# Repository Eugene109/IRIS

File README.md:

> A low-cost quadcopter platform designed for autonomous swarm operations.

## Overview
IRIS is centered around a mass-manufacturable low-cost PCB, containing a flight controller and 4 ESCs. Designed with the idea of delivering Skittles autonomously, IRIS is built from the ground-up for autonomous operation in swarms. With a rich sensor set and high degree of customizability, IRIS represents an accessible, low-cost entry into the world of autonomous and swarm drone operations. I began this project because I found a lack of accessible drone designs that are for more than just 'fun FPV flying', and I wanted to be able to program a drone to do cool things. IRIS represents a rethinking of small drone design, believing that small drones can and should be autonomous and that everyone should be able to program a drone.

## Features
 - STM32H743 MCU
 - IMU, Barometer, Magnetometer, GPS
 - Integrated 4-in-1 ESC with sensorless drive
 - OV2640 camera for computer vision
 - 2.4GHz Radio Transciever + nanoELRS header
 - 2S LiPo input, XT60 connector
 - 3D-printed frame

## Table of Contents
- [Design Features](#design-features)
  - [Flight Controller Design](#flight-controller-design)
  - [ESC Design](#esc-design)
  - [Frame Design](#frame-design)
- [Getting Started](#getting-started)
- [PCB Assembly](#pcb-assembly)
- [Bill of Materials](#bill-of-materials)
- [Drone Assembly](#drone-assembly)
- [Firmware](#firmware)
- [Roadmap](#roadmap)

## Hack Club Magazine Page

## Design Features

### Flight Controller Design
<p align="center">
  
&nbsp; &nbsp; &nbsp; &nbsp;
  
</p>

[Schematic](./pcb/schematics/Flight_Controller_Schematic.svg)

The PCB design features a 4-layer PCB stackup for lowered manufacturing costs, with a (nearly) continuous ground plane for reduced RF interference. The area under the MCU and core sensors also feature a continuous 3.3V power plane. The high voltage and current for the ESCs are routed on large copper pours on the bottom layer, with cross-layer connections connected by suture vias.

The total board dimensions are 3.650" by 2.856", a little larger than a credit card.

The main flight controller MCU is programmable over USB. The 4 ESC MCUs require a serial programmer, with ground, rx and tx exposed on header pins. All MCUs have a dedicated switch for a physical boot selector.

### ESC Design

[Schematic](./pcb/schematics/ESC_Schematics/Motor1_ESC_Schematic.svg)

The ESC design features an STM32F303K8T6 microcontroller, a very powerful MCU that enables accurate back-emf drive even for high kV motors. 

Loosely based off of this open-source design I found,
https://electronoobs.com/eng_arduino_tut91.php, the wiring diagram was very helpful to guide the general layout of my ESC. The control logic is loosely based off of the arduino code, though it had to be completely rewritten to interface with STM32 hardware (really all BLDC motor control logic is the same, but nice understandable code was helpful).

### Frame Design
The frame design merges swooping curves and sharp geometric angles in a retrofuturistic visual style. Inspired by the Theme Building at LAX, the frame arms are each constructed with 3 catenary curves, with the bottom arches merging together to form the cradle for the battery.

The bottom also features a -30º camera mount, which facilitates autonomous navigation, and turns into the perfect FPV mount when flown inverted.

At the top of the frame, a little cradle with a minimalist IRIS logo debossed reserves space for a small collection of Skittles, easily dumped out by flipping the drone.

The drone frame is constructed in two pieces and held together by 8 M2 screws. The bottom half contains a battery mount and 4 9x9mm motor mounts, while the top half clamps the PCB down. The top cover shields the bulk of the PCB while leaving the high-current ESC MOSFET sections exposed for cooling, and is bolted down using 8 10mm long M2 screws and heat set inserts on the bottom half.

## Getting Started

### Prerequisites

- EasyEDA Pro (recommended)
- KiCAD 10.0 (broken DRC rules)
- Fusion 360
- Blender 5.0+ ([pcb2blender](https://github.com/30350n/pcb2blender) extension required for textures)

### For KiCAD Users:
This project was made in the free software EasyEDA Pro, and the design is native to that software. The PCB design has been converted to a KiCAD project for easier access to the design, but there may be some errors that have occurred during the import process, in particular trace clearances and zone fill rules.

> NOTE: The KiCAD imported project relies on 3D models and footprints from LCSC, which were imported using [easyeda2kicad.py](https://github.com/uPesy/easyeda2kicad.py).

### Repository Structure
All of the files for the flight controller + ESC board are contained in `pcb/`, with fabrication files in `pcb/fabrication/`. All fabrication files are to [JLCPCB](https://jlcpcb.com/) specifications. All part numbers are from [LCSC](https://www.lcsc.com/).

The frame CAD files can be found in the `frame/` directory, with (metric) STL and 3MF exports ready for 3D printing. The cover and bottom were designed in the same Fusion360 Part, and the IRIS_Assembly.f3z is the total assembly including parts I did not design.

All of the renders on the documentation were created using Blender 5.1, and render files can be found in `docs/render/`.

## PCB Assembly

### PCB Component Bill of Materials
[PCB Component BOM](./pcb/fabrication/BOM.md)

Total cost from LCSC: **$103.21**
[LCSC Quote](./pcb/fabrication/LCSC_BOM_export.xls)

### Assembly

The [PCB gerbers](./pcb/fabrication/gerbers.zip) can be manufactured by JLCPCB with the simple 4-layer PCBA economical service. Two-sided automated assembly is quite expensive however, so first prototypes will be assembled manually using solder stencils. PCB components can be ordered from LCSC using the [LCSC BOM](./pcb/fabrication/BOM_Board1_PCB1.xlsx).
> NOTE: The large copper pours are connected directly to a lot of the pads, manual soldering will require the use of a hot air rework station and powerful soldering iron

## Bill of Materials
> Note: the full list of components for the PCB was not included in this BOM to save space, the component BOM can be found [here](./pcb/fabrication/BOM.md)

| Part | Description | Link | Price |
| --- | ----------- | ------------ | ----- |
| FC+ESC | 4-layer PCB A Economic, HASL(leaded) finish, 2 stencils w/ framework | [JLCPCB](https://cart.jlcpcb.com/quote) (Please upload ./pcb/fabrication/gerbers.zip to order the PCB) | 29.23 |
| FC+ESC | IRIS PCB Components | [LCSC](https://www.lcsc.com/) (Please upload ./pcb/fabrication/BOM_Board1_PCB1.xlsx to order the components) | 103.21 |
| Battery | 1000 mAh 2S LiPo with XT60 connector| [Admiral](https://motionrc.com/products/admiral-1000mah-2s-7-4v-30c-lipo-battery-with-xt60-connector-epr10002x6) | 9.99 |
| Motors | 4x 8000 kV 1103 Brushless DC | [AliExpress](https://www.aliexpress.us/item/3256808118156099.html) | 23.99 |
| Propellers | Gemfan 2512 2.5Inch 3-Blade 1.5mm Hole Propeller - 4CW+4CCW | [Pyrodrone](https://pyrodrone.com/products/gemfan-2512-2-5inch-3-blade-1-5mm-2mm-hole-propeller-4cw-4ccw) | 4.99 |
| Camera | OV2640 with SCCB cable | [AliExpress](https://www.aliexpress.us/item/3256805331385102.html) | 4.20 |
| Heat-set inserts | M2x2.5mm, 3.5mm OD Knurled Brass Threaded Heat Set Inserts | [Rusty Bolt Shop](https://ebay.us/m/7A3cL3) | 1.70 |
| Frame screws | M2x10mm screws | [The Rusty Bolt Shop](https://ebay.us/m/wMPMiQ) | 2.02 |
| Motor mount screws | M2x8mm screws | [The Rusty Bolt Shop](https://ebay.us/m/UnEsMj) | 2.56 |
| Vibration dampening foam | 3M Double Coated Urethane Foam Tape 4056 | [Newegg](https://www.newegg.com/p/2VW-0006-00155?item=9SIA5D52U89288) | 14.99 |

Total: $196.88
(minus shipping)

## Drone Assembly
1. Print the frame in two sections
2. Attach heat-set inserts with a soldering iron on the base half of the frame.
3. Cut 4056 foam to shape and attach to the PCB contact areas on both sides of the frame.
4. Attach the OV2640 camera SCCB cable to the connector and attach 4056 foam to the back of the sensor.
5. Insert the assembled PCB between the two frame sections and bolt down all 8 M2x10mm screws.
6. Slot the camera sensor into its 30º mount and attach using 4056 foam.
7. Insert the battery into the cradle underneath the PCB, mount it with 4056 foam and fasten down with zip ties across the horizontal beams, inside of the grooves.
8. Attach brushless motors with M2x8mm screws.
9. Press-fit 2CCW and 2CW propellers onto the four brushless motors' 1.5mm shafts.
10. Flash the [Betaflight firmware](./firmware/betaflight/binaries/betaflight_2026.6.0-alpha_STM32H743_IRIS_H743.hex) using a USB-C cable.
11. Flash the [Zephyrus firmware](https://github.com/Eugene109/zephyrus/releases/latest) to all four ESCs using a serial programmer attached to the 4-pin headers.
11. Fly!

## Firmware
### Betaflight
This flight controller is capable of running Betaflight, and the configuration header for a Betaflight target can be found in `firmware/betaflight/`. The compiled binaries can be found in the same directory, and the `.hex` file is recommended. The source code can be found at the [Betaflight firmware repository](https://github.com/betaflight/betaflight), and the `config.h` file can be copied into the config directory to build it yourself.

The flight control software can be flashed using the USB-C port on the aft of the drone. Simply plug it in and use STMCubeProgrammer to flash it!

### Zephyrus
The ESCs run custom firmware, named Zephyrus. The binaries and source code is available at its [repository](https://github.com/Eugene109/zephyrus).

Zephyrus is currently capable of sensorless back-EMF drive, and runs on the STM32F303K8T6 MCU platform. The sensorless drive is powered by ADC zero-crossing detection synchronized with the PWM output to the MOSFET drivers. The choice to use software detection of zero-crossing over hardware comparators was for the increased flexibility as the firmware matures, enabling more interesting control systems than just zero-crossing alone.

The ESCs are a bit harder to flash, though they should require only a single flashing when the firmware is tuned. Connect a serial programmer (FTDI, hijack an Arduino, etc) to the RX, TX, and GND pins and flash the MCU using the ROM bootloader. To switch the MCU to the built-in bootloader to program, simply flip the boot selector switch and press the reset button.

## Roadmap

- [X] PCB designed
- [X] Case designed
- [ ] PCB assembled
- [ ] Prototype assembled
- [ ] Prototype tested
- [ ] Firmware finalized
- [ ] PCB mass-produced

## License

Everything is [GNU GPL-3.0](LICENSE)

zephyrus firmware is licensed under MIT, check its [repo](https://github.com/Eugene109/zephyrus) for more information.

> **Trademark Notice:** Skittles® is a registered trademark of Mars, Inc. This project is not affiliated with, or sponsored by Mars, Inc. References to Skittles and any associated imagery are for descriptive purposes only.

### Attribution
1103 BLDC motor 3D model used in Fusion Assembly is from [GrabCAD](https://grabcad.com/library/geprc-gr1103-1) by [Dang Ngoc Duy](https://grabcad.com/dang.ngoc.duy-1)

2.5" propeller 3D model used in Fusion Assembly is from [GrabCAD](https://www.thingiverse.com/thing:6901068) by [Buddhas_Priest](https://www.thingiverse.com/Buddhas_Priest)

rostock_laage_airport_4k.exr is CC0 from PolyHaven, credit to Greg Zaal

Inspiration was taken from [Electronoobs's ESC design], informing the framework for a standard ESC architecture.

None of the PCB 3D models are my own work, they come from LCSC's libraries.

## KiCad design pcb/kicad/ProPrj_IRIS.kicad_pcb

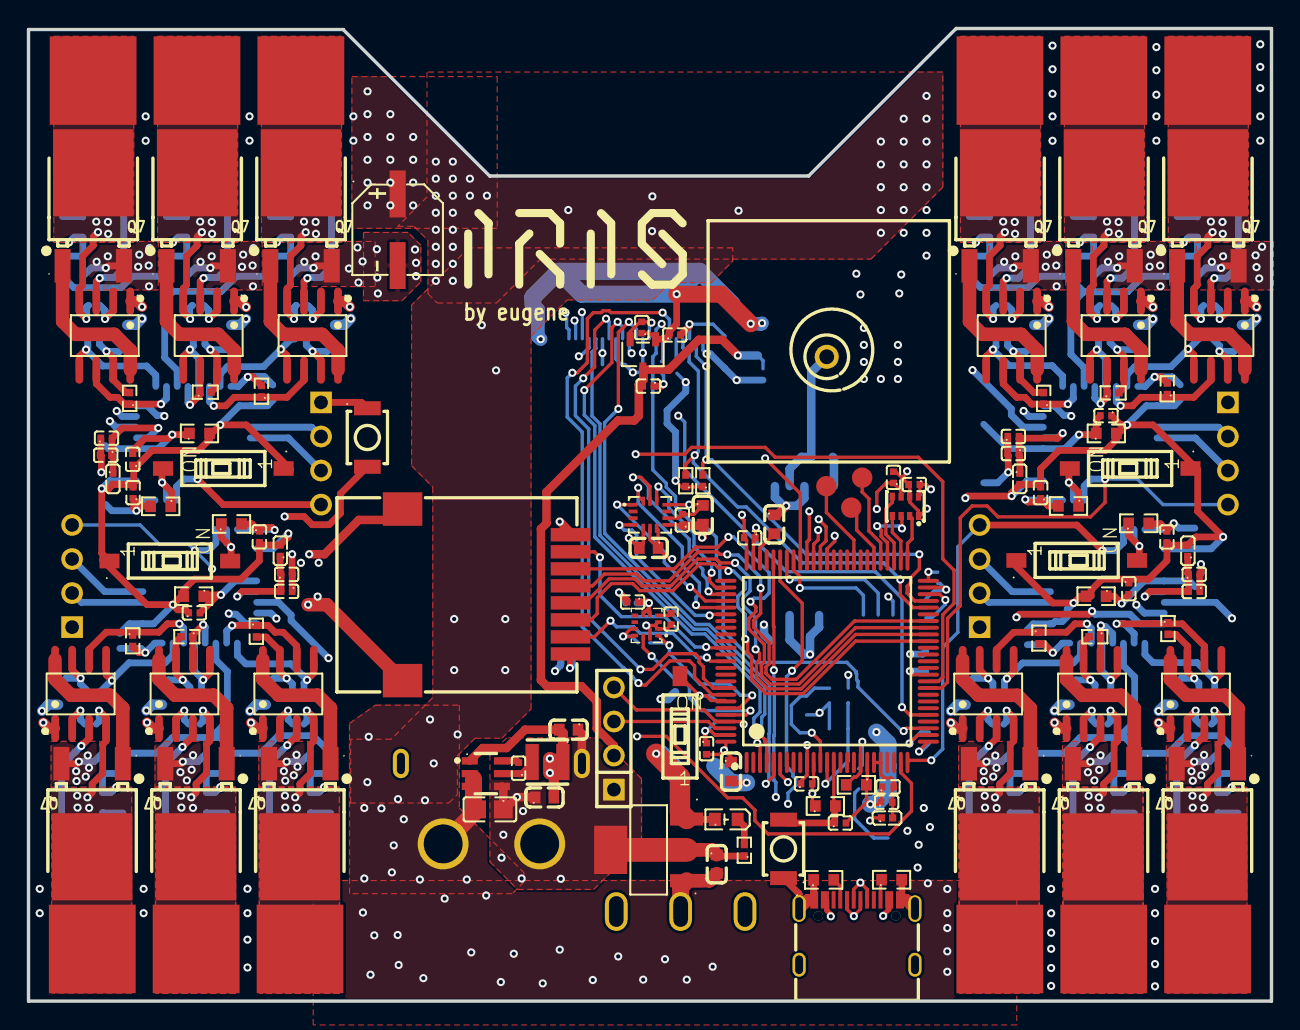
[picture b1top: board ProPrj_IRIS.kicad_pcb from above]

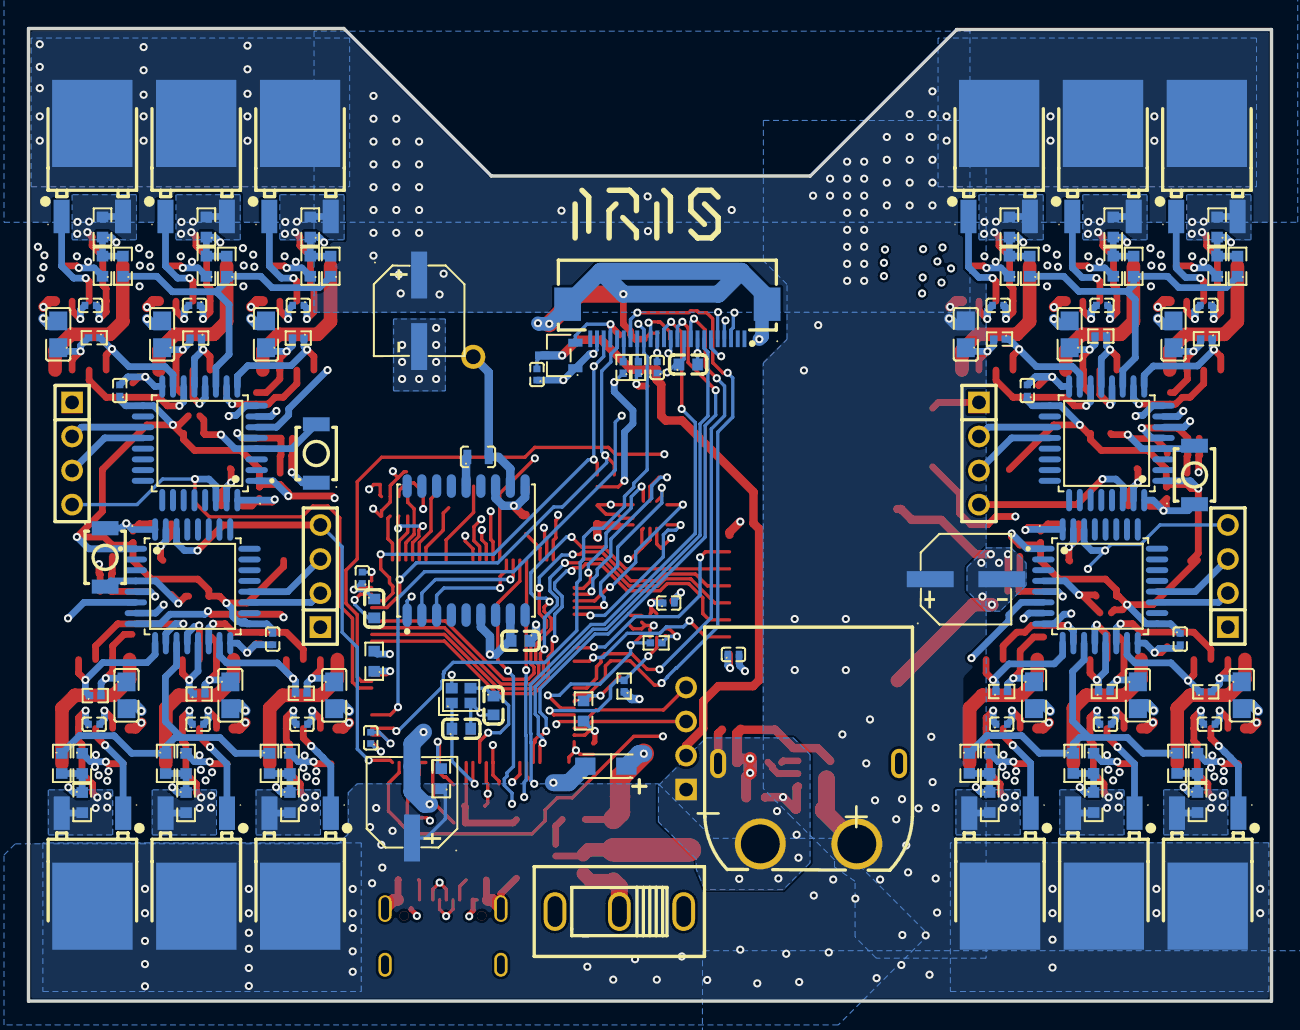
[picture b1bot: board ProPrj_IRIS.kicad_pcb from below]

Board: 4 copper layers, 92.7 x 72.5 mm, 244 parts (128 on the bottom side), 176 nets.

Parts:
C1, C25, C27, C94, C97, C98, C100, C103, C112, C113, C115, C116: C0603
C2, C3, C7, C8, C9, C10, C11, C12, C13, C14, C15, C16, C22, C24, C28, C29, C31, C32, C39, C40, C41, C43, C51, C52, C53, C54, C60, C61, C62, C63, C66, C67, C69, C71, C75, C76, C77, C78, C79, C80, C81, C89, C92, C93, C95, C105, C106, C107, C108, C109, C110, C114, C121: C0402
C4, C5, C6, C36, C37, C38, C55, C57, C58, C59, C68, C70, C96: C0805
C99: CAP-SMD_L3.2-W1.6-RD-C7171
C117, C118, C119, C120: CAP-SMD_BD6.3-L6.6-W6.6-LS7.2-FD_3
CN1: CONN-TH_XT60PW-M
FPC1: FPC-SMD_24P-P0.50_FPC-05F-24PH20
H1, H2, H3, H4, H5: HDR-TH_4P-HX-PH254-01-04-Z-L11.5
L1, L2, L3, L4, L5: L0402
L6: IND-SMD_L3.0-W3.0-1
L7: IND-SMD_L1.8-W1.0
L8: ANT-TH_L18.0-W18.0_C9900026472
Q1, Q2, Q3, Q4, Q5, Q6, Q7, Q8, Q9, Q10, Q11, Q12, Q13, Q14, Q15, Q16, Q17, Q18, Q19, Q20, Q21, Q22, Q23, Q24: TO-252-3_L6.6-W6.1-P4.57-LS9.9-BR-CW
R1, R2, R3, R4, R5, R6, R7, R8, R9, R10, R15, R16, R17, R19, R20, R21, R22, R23, R24, R28, R29, R30, R33, R34, R36, R41, R42, R43, R44, R45, R46, R47, R48, R49, R57, R58, R59, R60, R61, R62, R63, R64, R65, R66, R74, R75, R76, R81, R82, R84, R85: R0603
R11, R12, R13, R14, R18, R25, R26, R27, R31, R32, R37, R38, R39, R40, R50, R51, R52, R53, R54, R55, R67, R68, R69, R70, R71, R72, R77, R78, R79, R80, R83: R0402
SW1, SW2, SW3, SW4, SW5: SW-SMD_L3.9-W3.0-LS5.0
U1, U7, U10, U13, U14, U16, U17, U19, U20, U21, U22, U24: SOIC-8_L4.9-W3.9-P1.27-LS6.0-BL
U2: LGA-14_L3.0-W2.5-P0.50-TL
U3: LGA-8_L2.5-W2.0-P0.65_AMP6127
U4: LGA-12_L2.0-W2.0-P0.50-BL
U5, U6, U8, U12, U35: SW-SMD_2P-L6.2-W2.5-LS9.4
U9, U15, U18, U23: LQFP-32_L7.0-W7.0-P0.80-LS9.0-BL
U11: TSOT-23-6_L2.9-W1.6-P0.95-LS2.8-BL
U25: SOT-223-4_L6.5-W3.5-P2.30-LS7.0-BR
U27: GPSM-SMD_ATGM336H-TR
U29: SOT-23-3_L3.0-W1.6-P1.90-LS2.8-BR
U30: SOT-23-3_L2.9-W1.6-P1.90-LS2.8-BR
U31: CRYSTAL-SMD_4P-L2.0-W1.6-BL
U32: COMM-SMD_E01C-ML01SP4
U33: LQFP-100_L14.0-W14.0-P0.50-LS16.0-BL
U34: SW-TH_SHOU-HAN_SS12D10G4
U36: LED0603-FD
USB3: USB-C-SMD_KH-TYPE-C-16P

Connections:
1.2V: C108.2, FPC1.15, U29.2
2.8V: C109.2, FPC1.21, U30.2
3V3: C13.1, C14.1, C15.1, C16.1, C22.2, C25.2, C27.2, C28.1, C29.1, C31.1, C40.2, C43.1, C51.1, C52.1, C61.2, C63.1, C66.2, C75.1, C77.2, C78.2, C79.2, C80.2, C81.2, C94.1, C99.1, C100.2, C105.2, C106.1, C114.1, FPC1.14, L1.2, L2.2, L3.2, L4.1, L5.2, R2.2, R11.1, R12.1, R34.2, R36.2, R57.2, R76.1, R78.1, R79.1, R80.1, U2.5, U2.8, U3.6, U3.8, U4.5, U4.6, U4.9, U4.10, U5.1, U6.1, U8.1, U9.1, U9.17, U12.1, U15.1, U15.17, U18.1, U18.17, U23.1, U23.17, U25.3, U27.6, U27.8, U32.1, U33.6, U33.11, U33.27, U33.50, U33.75, U33.100, U35.1, U36.1
5V_USB: U34.3, USB3.A4, USB3.A9, USB3.B4, USB3.B9
7.4V_BATTERY: C4.2, C5.2, C6.2, C36.2, C37.2, C38.2, C55.2, C57.2, C58.2, C59.2, C68.2, C70.2, C96.2, C117.1, C118.1, C119.1, C120.1, CN1.2, Q1.2, Q3.2, Q5.2, Q8.2, Q9.2, Q11.2, Q14.2, Q15.2, Q17.2, Q20.2, Q21.2, Q23.2, R84.1, U1.1, U7.1, U10.1, U11.2, U11.3, U13.1, U14.1, U16.1, U17.1, U19.1, U20.1, U21.1, U22.1, U24.1
$1I45090\$1N2345: Q5.1, U22.3
$1I45090\$1N2351: Q4.1, U21.8
$1I45090\$1N2355: C69.2, U21.2
$1I45090\$1N2357: Q3.1, U21.3
$1I45090\$1N2360: Q2.1, U20.8
$1I45090\$1N2369: C67.2, U20.2
$1I45090\$1N2370: Q1.1, U20.3
$1I45090\$1N2393: C71.2, U22.2
$1I45090\$1N2396: Q6.1, U22.8
$1I45090\$1N2406: C2.2, C89.1, L3.1, U18.5
$1I45090\$1N39368: C13.2, R36.1, SW1.2, U18.4
$1I45090\AU: R19.1, R20.2, R21.2, U18.6
$1I45090\AV: R22.1, R23.2, R24.2, U18.7
$1I45090\AW: R28.1, R29.2, R30.2, U18.8
$1I45090\A_REF: R20.1, R23.1, R29.1, U18.11
$1I45090\BOOT0_ESC: R75.1, U18.31, U35.2
$1I45090\PHASE_U: C67.1, Q1.3, Q2.2, R19.2, U20.4
$1I45090\PHASE_V: C69.1, Q3.3, Q4.2, R22.2, U21.4
$1I45090\PHASE_W: C71.1, Q5.3, Q6.2, R28.2, U22.4
$1I45090\UH: R14.1, U18.9, U20.5
$1I45090\UL: R13.1, U18.10, U20.6
$1I45090\USART1_RX: H1.3, U18.20
$1I45090\USART1_TX: H1.2, U18.19
$1I45090\VH: R38.1, U18.13, U21.5
$1I45090\VL: R37.1, U18.12, U21.6
$1I45090\WH: R40.1, U18.15, U22.5
$1I45090\WL: R39.1, U18.14, U22.6
$1I45112\$1N2345: Q8.1, U1.3
$1I45112\$1N2351: Q7.1, U10.8
$1I45112\$1N2355: C24.2, U10.2
$1I45112\$1N2357: Q9.1, U10.3
$1I45112\$1N2360: Q10.1, U7.8
$1I45112\$1N2369: C7.2, U7.2
$1I45112\$1N2370: Q11.1, U7.3
$1I45112\$1N2393: C32.2, U1.2
$1I45112\$1N2396: Q12.1, U1.8
$1I45112\$1N2406: C3.1, C8.2, L1.1, U9.5
$1I45112\$1N39368: C14.2, R2.1, SW2.2, U9.4
$1I45112\AU: R8.1, R15.2, R17.2, U9.6
$1I45112\AV: R7.1, R9.2, R16.2, U9.7
$1I45112\AW: R4.2, R5.2, R6.1, U9.8
$1I45112\A_REF: R5.1, R16.1, R17.1, U9.11
$1I45112\BOOT0_ESC: R1.1, U5.2, U9.31
$1I45112\PHASE_U: C7.1, Q10.2, Q11.3, R8.2, U7.4
$1I45112\PHASE_V: C24.1, Q7.2, Q9.3, R7.2, U10.4
$1I45112\PHASE_W: C32.1, Q8.3, Q12.2, R6.2, U1.4
$1I45112\UH: R32.1, U7.5, U9.9
$1I45112\UL: R27.1, U7.6, U9.10
$1I45112\USART1_RX: H3.3, U9.20
$1I45112\USART1_TX: H3.2, U9.19
$1I45112\VH: R31.1, U9.13, U10.5
$1I45112\VL: R25.1, U9.12, U10.6
$1I45112\WH: R18.1, U1.5, U9.15
$1I45112\WL: R26.1, U1.6, U9.14
$1I45134\$1N2345: Q14.1, U13.3
$1I45134\$1N2351: Q13.1, U16.8
$1I45134\$1N2355: C41.2, U16.2
$1I45134\$1N2357: Q15.1, U16.3
$1I45134\$1N2360: Q16.1, U14.8
$1I45134\$1N2369: C39.2, U14.2
$1I45134\$1N2370: Q17.1, U14.3
$1I45134\$1N2393: C54.2, U13.2
$1I45134\$1N2396: Q18.1, U13.8
$1I45134\$1N2406: C9.2, C11.1, L2.1, U15.5
$1I45134\$1N39368: C15.2, R34.1, SW3.2, U15.4
$1I45134\AU: R45.1, R47.2, R49.2, U15.6
$1I45134\AV: R44.1, R46.2, R48.2, U15.7
$1I45134\AW: R41.2, R42.2, R43.1, U15.8
$1I45134\A_REF: R42.1, R48.1, R49.1, U15.11
$1I45134\BOOT0_ESC: R3.1, U6.2, U15.31
$1I45134\PHASE_U: C39.1, Q16.2, Q17.3, R45.2, U14.4
$1I45134\PHASE_V: C41.1, Q13.2, Q15.3, R44.2, U16.4
$1I45134\PHASE_W: C54.1, Q14.3, Q18.2, R43.2, U13.4
$1I45134\UH: R55.1, U14.5, U15.9
$1I45134\UL: R53.1, U14.6, U15.10
$1I45134\USART1_RX: H4.3, U15.20
$1I45134\USART1_TX: H4.2, U15.19
$1I45134\VH: R54.1, U15.13, U16.5
$1I45134\VL: R51.1, U15.12, U16.6
$1I45134\WH: R50.1, U13.5, U15.15
$1I45134\WL: R52.1, U13.6, U15.14
$1I45156\$1N2345: Q20.1, U17.3
$1I45156\$1N2351: Q19.1, U24.8
$1I45156\$1N2355: C62.2, U24.2
$1I45156\$1N2357: Q21.1, U24.3
$1I45156\$1N2360: Q22.1, U19.8
$1I45156\$1N2369: C60.2, U19.2
$1I45156\$1N2370: Q23.1, U19.3
$1I45156\$1N2393: C76.2, U17.2
$1I45156\$1N2396: Q24.1, U17.8
$1I45156\$1N2406: C10.2, C12.1, L5.1, U23.5
$1I45156\$1N39368: C16.2, R57.1, SW4.2, U23.4
$1I45156\AU: R62.1, R64.2, R66.2, U23.6
$1I45156\AV: R61.1, R63.2, R65.2, U23.7
$1I45156\AW: R58.2, R59.2, R60.1, U23.8
$1I45156\A_REF: R59.1, R65.1, R66.1, U23.11
$1I45156\BOOT0_ESC: R10.1, U8.2, U23.31
$1I45156\PHASE_U: C60.1, Q22.2, Q23.3, R62.2, U19.4
$1I45156\PHASE_V: C62.1, Q19.2, Q21.3, R61.2, U24.4
$1I45156\PHASE_W: C76.1, Q20.3, Q24.2, R60.2, U17.4
$1I45156\UH: R72.1, U19.5, U23.9
$1I45156\UL: R70.1, U19.6, U23.10
$1I45156\USART1_RX: H5.3, U23.20
$1I45156\USART1_TX: H5.2, U23.19
$1I45156\VH: R71.1, U23.13, U24.5
$1I45156\VL: R68.1, U23.12, U24.6
$1I45156\WH: R67.1, U17.5, U23.15
$1I45156\WL: R69.1, U17.6, U23.14
$1N17368: C97.2, C98.2, L6.2, U11.1, U34.1
$1N17546: C95.1, L6.1, U11.5
$1N56559: C95.2, U11.6
$1N79325: L7.2, L8.1, U27.11
$1N79329: L7.1, U27.14
$1N81168: FPC1.17, R77.2
$1N85586: R81.1, USB3.B5
$1N85625: R82.2, USB3.A5
$1N96765: C121.1, R76.2, SW5.2, U33.14
$1N102666: C115.2, U33.73
$1N105569: C116.2, U33.48
$1N119973: C53.2, U4.4
$1N130959: R83.2, U36.2
$1N133579: R84.2, R85.2, U33.18
+5V: C1.2, C107.2, C110.2, H2.2, U25.1, U29.3, U30.3, U34.2
BOOT0: R33.1, U12.2, U33.94
BOOT1: R74.1, U33.36
CAM_RST: FPC1.19, R78.2
CAM_XCLK: FPC1.12, U33.67
DCMI_0: FPC1.6, U33.63
DCMI_1: FPC1.4, U33.64
DCMI_2: FPC1.3, U33.65
DCMI_3: FPC1.5, U33.66
DCMI_4: FPC1.7, U33.3
DCMI_5: FPC1.9, U33.92
DCMI_6: FPC1.11, U33.4
DCMI_7: FPC1.13, U33.5
DCMI_HSYNC: FPC1.16, U33.28
DCMI_PXLCLK: C103.2, FPC1.8, U33.30
DCMI_VSYNC: FPC1.18, U33.93
DM: U33.70, USB3.A7, USB3.B7
DP: U33.71, USB3.A6, USB3.B6
E01_CE: U32.2, U33.88
E01_IRQ: U32.7, U33.86
GND: C1.1, C2.1, C3.2, C4.1, C5.1, C6.1, C8.1, C9.1, C10.1, C11.2, C12.2, C22.1, C25.1, C27.1, C28.2, C29.2, C31.2, C36.1, C37.1, C38.1, C40.1, C43.2, C51.2, C52.2, C53.1, C55.1, C57.1, C58.1, C59.1, C61.1, C63.2, C66.1, C68.1, C70.1, C75.2, C77.1, C78.1, C79.1, C80.1, C81.1, C89.2, C92.1, C93.1, C94.2, C96.1, C97.1, C98.1, C99.2, C100.1, C103.1, C105.1, C106.2, C107.1, C108.1, C109.1, C110.1, C112.2, C113.2, C114.2, C115.1, C116.1, C117.2, C118.2, C119.2, C120.2, C121.2, CN1.1, CN1.3, CN1.4, FPC1.10, FPC1.23, FPC1.25, FPC1.26, H1.1, H2.1, H3.1, H4.1, H5.1, Q2.3, Q4.3, Q6.3, Q7.3, Q10.3, Q12.3, Q13.3, Q16.3, Q18.3, Q19.3, Q22.3, Q24.3, R1.2, R3.2, R4.1, R9.1, R10.2, R13.2, R14.2, R15.1, R18.2, R21.1, R24.1, R25.2, R26.2, R27.2, R30.1, R31.2, R32.2, R33.2, R37.2, R38.2, R39.2, R40.2, R41.1, R46.1, R47.1, R50.2, R51.2, R52.2, R53.2, R54.2, R55.2, R58.1, R63.1, R64.1, R67.2, R68.2, R69.2, R70.2, R71.2, R72.2, R74.2, R75.2, R77.1, R81.2, R82.1, R83.1, R85.1, SW1.1, SW2.1, SW3.1, SW4.1, SW5.1, U1.7, U2.6, U2.7, U2.9, U2.11, U3.1, U3.7, U4.2, U4.3, U4.12, U7.7, U9.16, U9.32, U10.7, U11.4, U13.7, U14.7, U15.16, U15.32, U16.7, U17.7, U18.16, U18.32, U19.7, U20.7, U21.7, U22.7, U23.16, U23.32, U24.7, U25.2, U25.4, U27.1, U27.10, U27.12, U29.1, U30.1, U31.2, U31.4, U32.8, U32.9, U32.10, U33.10, U33.19, U33.26, U33.49, U33.74, U33.99, USB3.1, USB3.2, USB3.3, USB3.4, USB3.A1, USB3.A12, USB3.B1, USB3.B12
GPS_RX_MCU_TX: U27.3, U33.68
GPS_TX_MCU_RX: U27.2, U33.69
I2C1_SCLK: R12.2, U4.1, U33.95
I2C1_SDA: R11.2, U4.11, U33.96
I2C2_SCLK: FPC1.20, R80.2, U33.46
I2C2_SDA: FPC1.22, R79.2, U33.47
IMU_INT: U2.4, U33.81
MOTOR1: H1.4, U18.30, U33.34
MOTOR2: H3.4, U9.30, U33.35
MOTOR3: H5.4, U23.30, U33.24
MOTOR4: H4.4, U15.30, U33.25
RADIO_RX: H2.4, U33.97
RADIO_TX: H2.3, U33.98
SPI2_CS: U3.2, U33.51
SPI2_MISO: U3.5, U33.53
SPI2_MOSI: U3.3, U33.54
SPI2_SCLK: U3.4, U33.52
SPI3_CS: U2.12, U33.77
SPI3_MISO: U2.1, U33.79
SPI3_MOSI: U2.14, U33.80
SPI3_SCLK: U2.13, U33.78
SPI4_CS: U32.3, U33.41
SPI4_MISO: U32.6, U33.43
SPI4_MOSI: U32.5, U33.44
SPI4_SCLK: U32.4, U33.42
VDDA: C92.2, C93.2, L4.2, U33.20, U33.21
XI_HS: C113.1, U31.3, U33.12
XO_HS: C112.1, U31.1, U33.13

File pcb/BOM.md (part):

# Bill of Materials

| No. | Quantity | Comment                                    | Designator                                                                                                                                               | Footprint                            | Value | Manufacturer Part                          | Manufacturer           | Supplier Part | Supplier | LCSC Price | LCSC Stock | JLCPCB Price |
| --- | -------- | ------------------------------------------ | -------------------------------------------------------------------------------------------------------------------------------------------------------- | ------------------------------------ | ----- | ------------------------------------------ | ---------------------- | ------------- | -------- | ---------- | ---------- | ------------ |
| 1   | 2        | 10uF                                       | C1,C100                                                                                                                                                  | C0603                                | 10uF  | CL10A106KP8NNNC                            | SAMSUNG(三星)          | C19702        | LCSC     |            |            | 0.0012       |
| 2   | 10       | 1uF                                        | C2,C8,C9,C10,C51,C93,C107,C108,C109,C110                                                                                                                 | C0402                                | 1uF   | CL05A105KO5NNNC                            | SAMSUNG(三星)          | C29266        | LCSC     |            |            | 0.0005       |
| 3   | 38       | 100nF                                      | C3,C7,C11,C12,C22,C24,C28,C29,C31,C32,C39,C40,C41,C43,C52,C53,C54,C60,C61,C62,C63,C66,C67,C69,C71,C75,C76,C77,C78,C79,C80,C81,C89,C92,C95,C105,C106,C114 | C0402                                | 100nF | CC0402X7R25V104KN                          | TORCH(火炬)            | C53084459     | LCSC     |            |            | 0.0004       |
| 4   | 12       | 22uF                                       | C4,C5,C6,C36,C37,C38,C55,C57,C58,C59,C68,C70                                                                                                             | C0805                                | 22uF  | CL21A226MAYNNNE                            | SAMSUNG(三星)          | C602037       | LCSC     |            |            | 0.005        |
| 5   | 3        | 2.2uF                                      | C25,C115,C116                                                                                                                                            | C0603                                | 2.2uF | CL10A225KO8NNNC                            | SAMSUNG(三星)          | C23630        | LCSC     |            |            | 0.001        |
| 6   | 1        | 10nF                                       | C27                                                                                                                                                      | C0603                                | 10nF  | CC0603KRX7R9BB103                          | YAGEO(国巨)            | C100042       | LCSC     |            |            | 0.0004       |
| 7   | 1        | 4.7uF                                      | C94                                                                                                                                                      | C0603                                | 4.7uF | CL10A475KO8NNNC                            | SAMSUNG(三星)          | C19666        | LCSC     |            |            | 0.0015       |
| 8   | 1        | 10uF                                       | C96                                                                                                                                                      | C0805                                | 10uF  | CL21B106KOQNNNE                            | SAMSUNG(三星)          | C95841        | LCSC     |            |            | 0.0041       |
| 9   | 2        | 22uF                                       | C97,C98                                                                                                                                                  | C0603                                | 22uF  | CL10A226MP8NUNE                            | SAMSUNG(三星)          | C86295        | LCSC     |            |            | 0.0022       |
| 10  | 1        | 10uF                                       | C99                                                                                                                                                      | CAP-SMD_L3.2-W1.6-RD-C7171           | 10uF  | TAJA106K016RNJ                             | Kyocera AVX            | C7171         | LCSC     |            |            | 0.0211       |
| 11  | 1        | 15pF                                       | C103                                                                                                                                                     | C0603                                | 15pF  | CL10C150JB8NNNC                            | SAMSUNG(三星)          | C1644         | LCSC     |            |            | 0.0008       |
| 12  | 2        | 10pF                                       | C112,C113                                                                                                                                                | C0603                                | 10pF  | CC0603JRNPO9BN100                          | YAGEO(国巨)            | C106245       | LCSC     |            |            | 0.0005       |
| 13  | 4        | 330uF                                      | C117,C118,C119,C120                                                                                                                                      | CAP-SMD_BD6.3-L6.6-W6.6-LS7.2-FD_3   | 330uF | RVT16V330M6X8                              | JIERR(捷而瑞)          | C47023104     | LCSC     |            |            | 0.0079       |
| 14  | 1        | XT60PW-M                                   | CN1                                                                                                                                                      | CONN-TH_XT60PW-M                     |       | XT60PW-M                                   | AMASS(艾迈斯)          | C98732        | LCSC     |            |            | 0.0763       |
| 15  | 1        | FPC-05F-24PH20                             | FPC1                                                                                                                                                     | FPC-SMD_24P-P0.50_FPC-05F-24PH20     |       | FPC-05F-24PH20                             | XUNPU(讯普)            | C2856805      | LCSC     |            |            | 0.0148       |
| 16  | 5        | HX PH254-01-04-Z-L11.5 straight pin header | H1,H2,H3,H4,H5                                                                                                                                           | HDR-TH_4P-HX-PH254-01-04-Z-L11.5     |       | HX PH254-01-04-Z-L11.5 straight pin header | hanxia(韩下)           | C52016392     | LCSC     |            |            | 0.0045       |
| 17  | 5        | BLM15PD121SN1D                             | L1,L2,L3,L4,L5                                                                                                                                           | L0402                                |       | BLM15PD121SN1D                             | muRata(村田)           | C76891        | LCSC     |            |            | 0.0017       |
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
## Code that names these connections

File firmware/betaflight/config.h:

/*
 * This file is part of Betaflight.
 *
 * Betaflight is free software. You can redistribute this software
 * and/or modify this software under the terms of the GNU General
 * Public License as published by the Free Software Foundation,
 * either version 3 of the License, or (at your option) any later
 * version.
 *
 * Betaflight is distributed in the hope that it will be useful,
 * but WITHOUT ANY WARRANTY; without even the implied warranty of
 * MERCHANTABILITY or FITNESS FOR A PARTICULAR PURPOSE.
 *
 * See the GNU General Public License for more details.
 *
 * You should have received a copy of the GNU General Public
 * License along with this software.
 *
 * If not, see <http://www.gnu.org/licenses/>.
 */

#pragma once

#define FC_TARGET_MCU     STM32H743
#define BOARD_NAME IRIS
#define MANUFACTURER_ID EUGENE_IS_AWESOME

#define USE_ACC
#define USE_ACC_SPI_ICM42688P
#define USE_GYRO
#define USE_GYRO_SPI_ICM42688P
#define USE_BARO
#define USE_BARO_SPI_BMP280
#define USE_MAG
#define USE_MAG_LIS3MDL
// #define USE_FLASH
// #define USE_FLASH_M25P16
// #define USE_MAX7456

// #define BEEPER_PIN PD15
#define MOTOR1_PIN PB0
#define MOTOR2_PIN PB1
#define MOTOR3_PIN PA2
#define MOTOR4_PIN PA3
// #define RX_PPM_PIN PA3
// #define LED_STRIP_PIN PD12
#define UART1_TX_PIN PA9  // GPS
#define UART2_TX_PIN PA2
#define UART3_TX_PIN PB10
#define UART4_TX_PIN PA0
#define UART6_TX_PIN PC6
#define UART7_TX_PIN PE8
#define UART8_TX_PIN PE1  // nanoELRS
#define UART1_RX_PIN PA10 // GPS 
#define UART2_RX_PIN PA3
#define UART3_RX_PIN PB11
#define UART4_RX_PIN PA1
#define UART6_RX_PIN PC7
#define UART7_RX_PIN PE7
#define UART8_RX_PIN PE0  // nanoELRS
#define I2C1_SCL_PIN PB8
#define I2C1_SDA_PIN PB9
// #define I2C2_SCL_PIN PB10 // OV2640 camera
// #define I2C2_SDA_PIN PB11 // OV2640 camera
#define LEPD_PIN PC13

#define SPI1_SCK_PIN PA5
#define SPI1_SDI_PIN PA6
#define SPI1_SDO_PIN PA7

#define SPI2_SCK_PIN PB13
#define SPI2_SDI_PIN PB14
#define SPI2_SDO_PIN PB15

#define SPI3_SCK_PIN PC10
#define SPI3_SDI_PIN PC11
#define SPI3_SDO_PIN PC12

#define SPI4_SCK_PIN PE12
#define SPI4_SDI_PIN PE13
#define SPI4_SDO_PIN PE14
// #define CAMERA_CONTROL_PIN PC8
#define ADC_VBAT_PIN PC3
#define ADC_RSSI_PIN PC5
#define ADC_CURR_PIN PC2
// #define FLASH_CS_PIN PA15
// #define MAX7456_SPI_CS_PIN PE4
#define GYRO_1_EXTI_PIN PD0
#define GYRO_1_CS_PIN PA15
#define BARO_CS_PIN PB12

#define TIMER_PIN_MAPPING \
    TIMER_PIN_MAP( 3, PB0,  2,  0 ) \
    TIMER_PIN_MAP( 4, PB1,  2,  1 ) \
    TIMER_PIN_MAP( 5, PA2,  1,  2 ) \
    TIMER_PIN_MAP( 6, PA3,  1,  3 ) \

// TIMER_PIN_MAP( 0, PD12, 1, 10 )
// TIMER_PIN_MAP( 1, PA3,  1,  0 )
// TIMER_PIN_MAP( 2, PC8,  2,  0 ) 

#define ADC1_DMA_OPT 8
#define ADC3_DMA_OPT 9
#define TIMUP1_DMA_OPT 0
#define TIMUP2_DMA_OPT 0
#define TIMUP3_DMA_OPT 0
#define TIMUP4_DMA_OPT 0
#define TIMUP8_DMA_OPT 0

#define BARO_SPI_INSTANCE SPI2
#define MAG_I2C_INSTANCE I2CDEV_1
#define ADC_INSTANCE ADC1
// #define DEFAULT_BLACKBOX_DEVICE BLACKBOX_DEVICE_FLASH
#define DEFAULT_CURRENT_METER_SOURCE CURRENT_METER_ADC
#define DEFAULT_VOLTAGE_METER_SOURCE VOLTAGE_METER_ADC
#define DEFAULT_VOLTAGE_METER_SCALE 110
#define DEFAULT_CURRENT_METER_SCALE 200
// #define BEEPER_INVERTED
// #define MAX7456_SPI_INSTANCE SPI4
// #define FLASH_SPI_INSTANCE SPI3
#define GYRO_1_SPI_INSTANCE SPI3

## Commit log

2026-04-06 renamed project
    skittles
2026-04-15 STM32F407 design backup
2026-04-20 finished PCB, slightly oversized
2026-04-30 PCB Version 2, 50% size reduction + finished gerbers
2026-05-01 (minor fix for PCB V2) CAM_XCLK connected
2026-05-01 Basic info for README
2026-05-03 Moved the 5V power switch for the frame mount
2026-05-04 Fixed camera placement and finalized PCB component BOM
2026-05-04 Reorganized README
2026-05-04 Moved boot selector switches for easier soldering
2026-05-04 converted PCB design to KiCAD + blender 3D model for renders
2026-05-04 packed external data
2026-05-05 flipped XT60 connector to bottom + photorealistic renders
2026-05-06 3D printable drone frame
2026-05-06 reorganized repository
2026-05-06 drone frame assembly, components, design
2026-05-07 firmware for flight controller
2026-05-08 Cool logo design
2026-05-10 updates to ESC, quality-of-life improvements to the PCB, redesigned frame top, more photorealistic renders
2026-05-10 fix logo format in README.md
2026-05-10 completed drone assembly
2026-05-10 improved bill of materials
2026-05-11 'hero shot' render + orthogonal renders + updated README
2026-05-11 camera attachment point + zip tie grooves
2026-05-12 magazine page
2026-05-12 cleaned up README
2026-05-12 corrected nrst decoupling capacitor - thanks to @kaipereira for the tip
2026-05-12 Fix URLs in BOM.csv for better accessibility
    Updated links in BOM.csv to direct URLs, fallout automated checks did not like my old BOM
2026-05-12 Update BOM.csv to remove formatting characters
2026-05-12 Fix links for PCB components in README
    Updated links for JLCPCB and LCSC in the Bill of Materials.
2026-05-12 Add LCSC link column to BOM_Board1_PCB1.csv
2026-05-12 correct 100nF capacitor details in BOM
    copilot hallucinated while trying to appease Fallout AI hallucinations
2026-05-12 Add BOM_Board1_PCB1.csv file
2026-05-12 Delete pcb/fabrication/BOM_Board1_PCB1.csv
    This might be tripping up the Fallout AI? I'm grasping at straws here
2026-05-12 Fix README
2026-05-12 Add supplier part links to BOM
    Updated BOM with supplier part links for components.
2026-05-12 Bill of Materials link issues clarified
2026-05-12 commas instead of tabs
2026-05-12 swapped OV2640 part - also a small justification in Overview

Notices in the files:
README.md:
License: GNU
